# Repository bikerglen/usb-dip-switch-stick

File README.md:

# usb-dip-switch-stick
Use the DIP Switch USB Stick for when your application needs configuration settings but a JSON or XML file on disk is overkill.

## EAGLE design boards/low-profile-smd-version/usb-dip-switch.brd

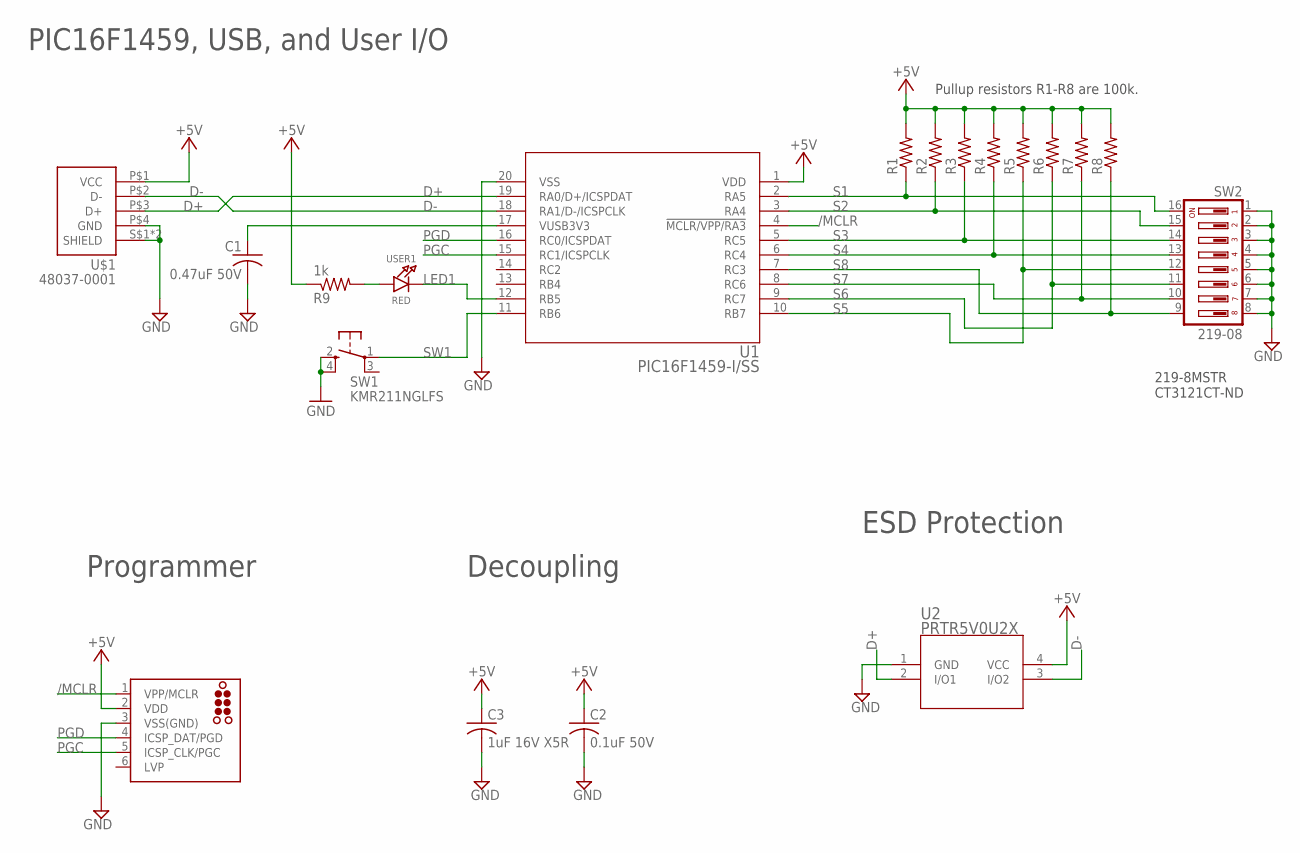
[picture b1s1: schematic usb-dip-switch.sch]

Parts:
C1: 0.47uF 50V; C1206K; MFR_PART_NO C1206C474K5RACTU
C2: 0.1uF 50V; C0603; MFR_PART_NO C1206S104M5RACTU
C3: 1uF 16V X5R; C0603; MFR_PART_NO C1210C105K4PACTU
J3: TC2030-MCP-NL
R1, R2, R3, R4, R5, R6, R7, R8: 100k; R0603
R9: 1k; R0805
SW1: KMR211NGLFS; KMR2
SW2: 219-08; CTS-219-08
U1: PIC16F1459-I/SS; SSOP20_MC
U2: PRTR5V0U2X; SOT143B
U$1: 48037-0001
USER1: RED; CHIPLED_0805_NOOUTLINE

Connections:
+5V: C2.1, C3.1, J3.2 (VDD), R1.2, R2.2, R3.2, R4.2, R5.2, R6.2, R7.2, R8.2, R9.1, U1.1 (VDD), U2.4 (VCC), U$1.P$1 (VCC)
/MCLR: J3.1 (VPP/MCLR), U1.4 (!MCLR/VPP/RA3)
D+: U1.19 (RA0/D+/ICSPDAT), U2.2 (I/O1), U$1.P$3 (D+)
D-: U1.18 (RA1/D-/ICSPCLK), U2.3 (I/O2), U$1.P$2 (D-)
GND: C1.2, C2.2, C3.2, J3.3 (VSS(GND)), SW1.2 (S), SW1.4 (S1), SW2.1, SW2.2, SW2.3, SW2.4, SW2.5, SW2.6, SW2.7, SW2.8, U1.20 (VSS), U2.1 (GND), U$1.P$4 (GND), U$1.S$1 (SHIELD), U$1.S$2 (SHIELD)
LED1: U1.12 (RB5), USER1.C
unnamed: R9.2, USER1.A
PGC: J3.5 (ICSP_CLK/PGC), U1.15 (RC1/ICSPCLK)
PGD: J3.4 (ICSP_DAT/PGD), U1.16 (RC0/ICSPDAT)
S1: R1.1, SW2.16, U1.2 (RA5)
S2: R2.1, SW2.15, U1.3 (RA4)
S3: R3.1, SW2.14, U1.5 (RC5)
S4: R4.1, SW2.13, U1.6 (RC4)
S5: R5.1, SW2.12, U1.10 (RB7)
S6: R6.1, SW2.11, U1.9 (RC7)
S7: R7.1, SW2.10, U1.8 (RC6)
S8: R8.1, SW2.9, U1.7 (RC3)
SW1: SW1.1, U1.11 (RB6)
VUSB1: C1.1, U1.17 (VUSB3V3)

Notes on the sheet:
PIC16F1459, USB, and User I/O
Programmer
Decoupling
ESD Protection
219-8MSTR CT3121CT-ND
Pullup resistors R1-R8 are 100k.

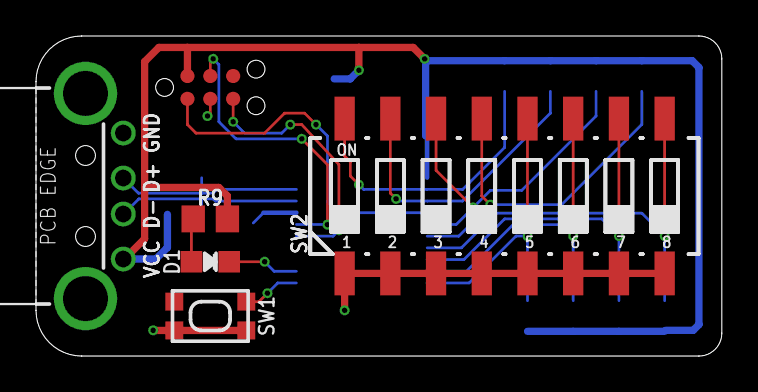
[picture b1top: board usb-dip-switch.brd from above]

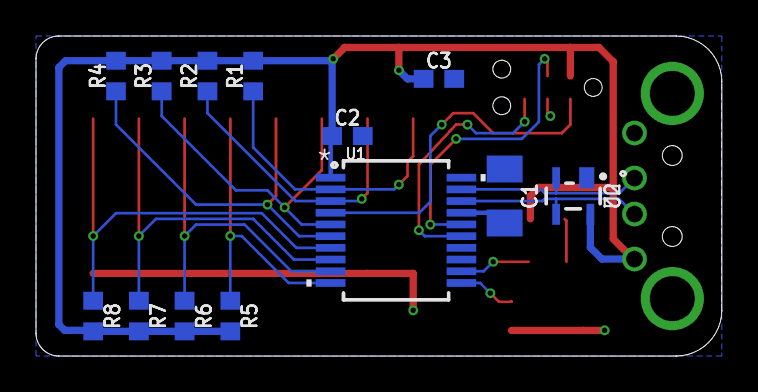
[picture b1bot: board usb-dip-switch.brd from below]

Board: 2 copper layers, 38.1 x 17.8 mm, 19 parts (13 on the bottom side), 19 nets.

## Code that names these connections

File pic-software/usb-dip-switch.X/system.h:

/*******************************************************************************
Copyright 2016 Microchip Technology Inc. (www.microchip.com)

Licensed under the Apache License, Version 2.0 (the "License");
you may not use this file except in compliance with the License.
You may obtain a copy of the License at

    http://www.apache.org/licenses/LICENSE-2.0

Unless required by applicable law or agreed to in writing, software
distributed under the License is distributed on an "AS IS" BASIS,
WITHOUT WARRANTIES OR CONDITIONS OF ANY KIND, either express or implied.
See the License for the specific language governing permissions and
limitations under the License.

To request to license the code under the MLA license (www.microchip.com/mla_license), 
please contact mla_licensing@microchip.com
*******************************************************************************/

#ifndef SYSTEM_H
#define SYSTEM_H

// #define DEV_BOARD

#include <xc.h>
#include <stdbool.h>

#include "fixed_address_memory.h"

#define USE_INTERNAL_OSC

#define MAIN_RETURN void

// 250 Hz timer 2 period value
// dec2hex(12e6/16/12/250-1)
#define TMR2_PERIOD 0xF9

#ifdef DEV_BOARD
#define SW2      (PORTCbits.RC5 ? 0 : 1)
#define USER_LED LATCbits.LATC3
#define LED_ON 1
#define LED_OFF 0
#else

// GPIO input pins
#define PB1      (PORTBbits.RB6 ? 0 : 1)
#define SW1      (PORTAbits.RA5 ? 0 : 1)
#define SW2      (PORTAbits.RA4 ? 0 : 1)
#define SW3      (PORTCbits.RC5 ? 0 : 1)
#define SW4      (PORTCbits.RC4 ? 0 : 1)
#define SW5      (PORTBbits.RB7 ? 0 : 1)
#define SW6      (PORTCbits.RC7 ? 0 : 1)
#define SW7      (PORTCbits.RC6 ? 0 : 1)
#define SW8      (PORTCbits.RC3 ? 0 : 1)

// GPIO output pins
#define USER_LED LATBbits.LATB5

// led states
#define LED_ON   0
#define LED_OFF  1
#endif


/*** System States **************************************************/
typedef enum {
    SYSTEM_STATE_USB_START,
    SYSTEM_STATE_USB_SUSPEND,
    SYSTEM_STATE_USB_RESUME
} SYSTEM_STATE;

/*********************************************************************
* Function: void SYSTEM_Initialize( SYSTEM_STATE state )
*
* Overview: Initializes the system.
*
* PreCondition: None
*
* Input:  SYSTEM_STATE - the state to initialize the system into
*
* Output: None
*
********************************************************************/
void SYSTEM_Initialize( SYSTEM_STATE state );


/*********************************************************************
* Function: void SYSTEM_Tasks(void)
*
* Overview: Runs system level tasks that keep the system running
*
* PreCondition: System has been initialized with SYSTEM_Initialize()
*
* Input: None
*
* Output: None
*
********************************************************************/
//void SYSTEM_Tasks(void);
#define SYSTEM_Tasks()

void TMR2_Initialize (void);
void TMR2_InterruptHandler (void);

#endif //SYSTEM_H

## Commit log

2022-01-16 initial checkin
2022-01-16 move windows files to correct directory
2022-01-16 add README with link to HidLibrary on Github
2022-01-16 add README with IDE and XC8 versions
2022-02-21 add 100k value for pullup resistors R1-R8
2022-02-21 re-adding pic-software directory since it seemed to have disappeared
2022-02-21 add 100k value to pullup resistors R1-R8

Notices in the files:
parts and their libraries:
tag-connect: ©2009 ROFA.cz - modified and updated by Robert Darlington ‹rdarlington@gmail.com›
microbuilder: This work is placed in the public domain, and may be freely used for commercial and non-commercial work with the following conditions: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
